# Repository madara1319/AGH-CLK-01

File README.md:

# AGH-CLK-01

Project of embedded wristwatch module powered by li-pol cell realised for University course Design-Laboratory
## Project assumptions
The main goal is to make self-contained embedded wristwatch module that could be used with dedicated wrist as a complete wristwatch. That device will have his own supply made by li-pol cell with dedicated hardware driver. As a display will be used full color LCD screen module with 240x240px and ST7789 driver. Device will be controlled by microprocessor STM32 (particular type will be pick in time) that would be placed on a dedicated printed circuit board “AGH-CLK-01” with the rest of peripherals. Everything should be assembled as a ready-to-use device.

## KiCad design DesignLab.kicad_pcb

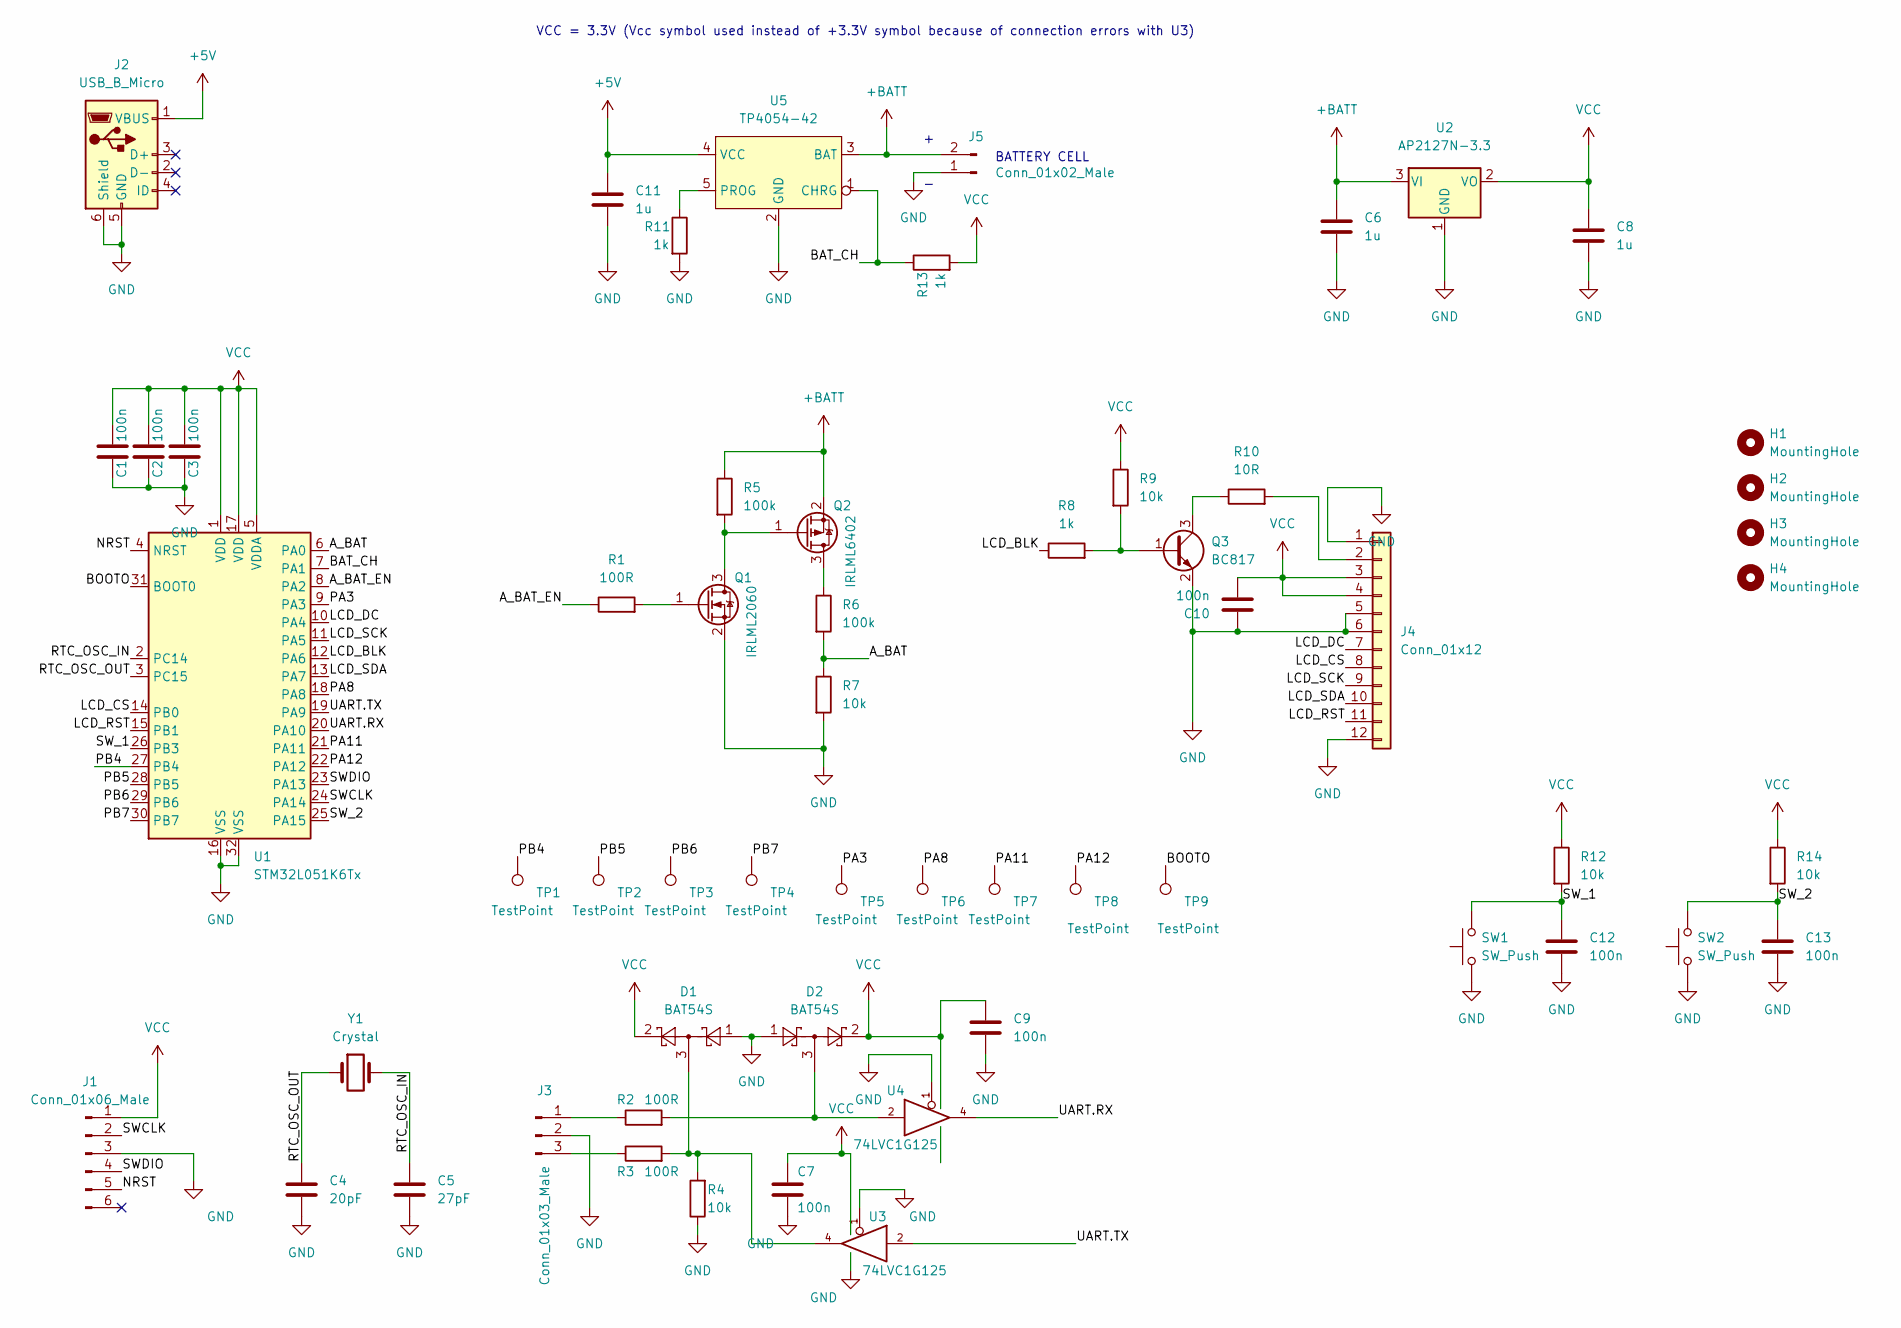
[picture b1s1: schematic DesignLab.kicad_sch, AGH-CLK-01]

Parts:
C1, C2, C3: 100n; C_0603_1608Metric_Pad1.08x0.95mm_HandSolder
C4: 20pF; C_0603_1608Metric_Pad1.08x0.95mm_HandSolder
C5: 27pF; C_0603_1608Metric_Pad1.08x0.95mm_HandSolder
C6, C8: 1u; C_0805_2012Metric_Pad1.18x1.45mm_HandSolder
C7, C9, C10, C12, C13: 100n; C_0805_2012Metric_Pad1.18x1.45mm_HandSolder
C11: 1u; C_1206_3216Metric_Pad1.33x1.80mm_HandSolder
D1, D2: BAT54S; SOT-23
H1, H2, H3, H4: MountingHole; MountingHole_2.2mm_M2_ISO7380
J1: Conn_01x06_Male; PinHeader_2x03_P2.54mm_Vertical
J2: USB_B_Micro; USB_Micro-B_Amphenol_10118194_Horizontal
J3: Conn_01x03_Male; PinHeader_1x03_P2.54mm_Vertical
J4: Conn_01x12; Flex_Tape_12x0.635
J5: Conn_01x02_Male; PinHeader_1x02_P2.54mm_Vertical
Q1: IRLML2060; SOT-23
Q2: IRLML6402; SOT-23
Q3: BC817; SOT-23
R1, R2, R3: 100R; R_0603_1608Metric_Pad0.98x0.95mm_HandSolder
R4, R7, R9, R12, R14: 10k; R_0603_1608Metric_Pad0.98x0.95mm_HandSolder
R5, R6: 100k; R_0603_1608Metric_Pad0.98x0.95mm_HandSolder
R8, R11, R13: 1k; R_0603_1608Metric_Pad0.98x0.95mm_HandSolder
R10: 10R; R_0603_1608Metric_Pad0.98x0.95mm_HandSolder
SW1, SW2: SW_Push; SW_SPST_TSS02-035NT
TP1, TP2, TP3, TP4, TP5, TP6, TP7, TP8, TP9: TestPoint; TestPoint_Pad_1.5x1.5mm
U1: STM32L051K6Tx; LQFP-32_7x7mm_P0.8mm
U2: AP2127N-3.3; SOT-23
U3, U4: 74LVC1G125; SOT-23-5_HandSoldering
U5: TP4054-42; SOT-23-5_HandSoldering
Y1: Crystal; Crystal_SMD_3215-2Pin_3.2x1.5mm

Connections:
+5V: C11.1, J2.1 (VBUS), U5.4 (VCC)
+BATT: C6.1, J5.2, Q2.2 (S), R5.1, U2.3 (VI), U5.3 (BAT)
/A_BAT: R6.2, R7.1, U1.6 (PA0)
/A_BAT_EN: R1.1, U1.8 (PA2)
/BAT_CH: R13.1, U1.7 (PA1), U5.1 (CHRG)
/BOOTO: TP9.1, U1.31 (BOOT0)
/LCD_BLK: R8.1, U1.12 (PA6)
/LCD_CS: J4.8, U1.14 (PB0)
/LCD_DC: J4.7, U1.10 (PA4)
/LCD_RST: J4.11, U1.15 (PB1)
/LCD_SCK: J4.9, U1.11 (PA5)
/LCD_SDA: J4.10, U1.13 (PA7)
/NRST: J1.5, U1.4 (NRST)
/PA3: TP5.1, U1.9 (PA3)
/PA8: TP6.1, U1.18 (PA8)
/PA11: TP7.1, U1.21 (PA11)
/PA12: TP8.1, U1.22 (PA12)
/PB4: TP1.1, U1.27 (PB4)
/PB5: TP2.1, U1.28 (PB5)
/PB6: TP3.1, U1.29 (PB6)
/PB7: TP4.1, U1.30 (PB7)
/RTC_OSC_IN: C5.1, U1.2 (PC14), Y1.2
/RTC_OSC_OUT: C4.1, U1.3 (PC15), Y1.1
/SWCLK: J1.2, U1.24 (PA14)
/SWDIO: J1.4, U1.23 (PA13)
/SW_1: C12.1, R12.2, SW1.2, U1.26 (PB3)
/SW_2: C13.1, R14.2, SW2.2, U1.25 (PA15)
/UART.RX: U1.20 (PA10), U4.4
/UART.TX: U1.19 (PA9), U3.2
GND: C1.2, C2.2, C3.2, C4.2, C5.2, C6.2, C7.2, C8.2, C9.2, C10.1, C11.2, C12.2, C13.2, D1.1, D2.1, J1.3, J2.5 (GND), J2.6 (Shield), J3.2, J4.1, J4.5, J4.6, J4.12, J5.1, Q1.2 (S), Q3.2 (E), R4.1, R7.2, R11.2, SW1.1, SW2.1, U1.16 (VSS), U1.32 (VSS), U2.1 (GND), U3.1, U3.3 (GND), U4.1, U4.3 (GND), U5.2 (GND)
unnamed: D1.3, R3.2, R4.2, U3.4
unnamed: D2.3, R2.2, U4.2
unnamed: J3.1, R2.1
unnamed: J3.3, R3.1
unnamed: J4.2, R10.2
unnamed: Q1.1 (G), R1.2
unnamed: Q1.3 (D), Q2.1 (G), R5.2
unnamed: Q2.3 (D), R6.1
unnamed: Q3.1 (B), R8.2, R9.2
unnamed: Q3.3 (C), R10.1
unnamed: R11.1, U5.5 (PROG)
VCC: C1.1, C2.1, C3.1, C7.1, C8.1, C9.1, C10.2, D1.2, D2.2, J1.1, J4.3, J4.4, R9.1, R12.1, R13.2, R14.1, U1.1 (VDD), U1.5 (VDDA), U1.17 (VDD), U2.2 (VO), U3.5 (VCC), U4.5 (VCC)

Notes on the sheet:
VCC = 3.3V (Vcc symbol used instead of +3.3V symbol because of connection errors with U3)
BATTERY CELL

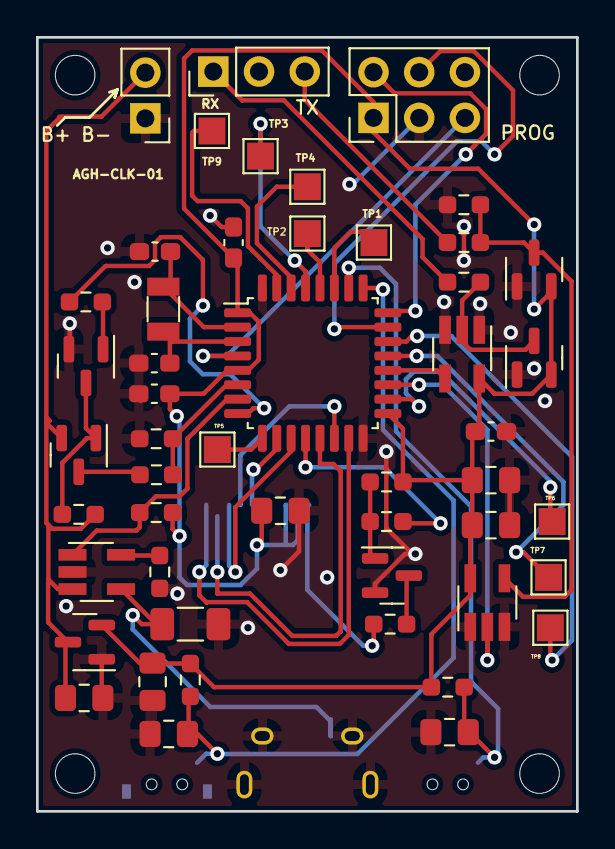
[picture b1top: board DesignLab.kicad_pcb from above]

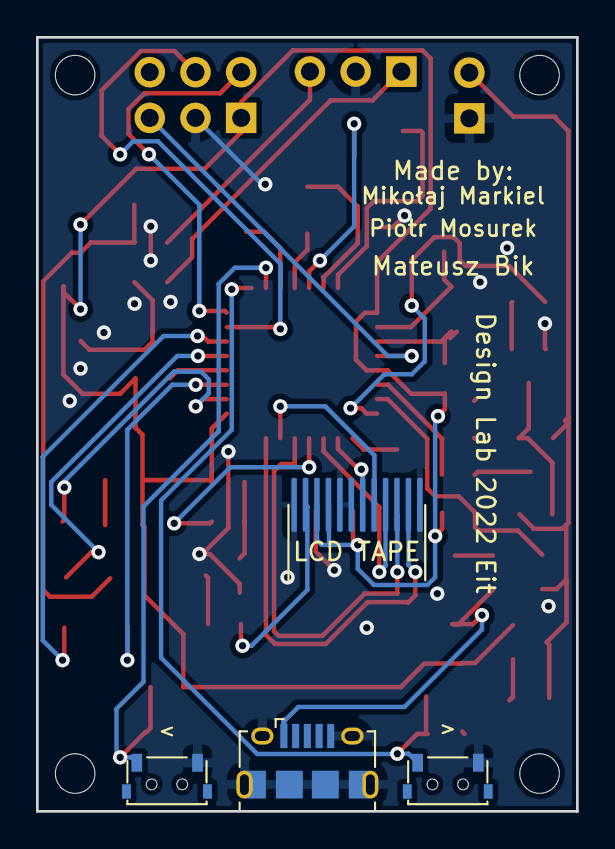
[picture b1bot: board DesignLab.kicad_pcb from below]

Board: 2 copper layers, 30.0 x 43.0 mm, 58 parts (4 on the bottom side), 42 nets.

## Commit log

2022-12-01 Added readme
2022-12-01 Still needs work with connecting correct pins, buffers etc
2022-12-06 v0.2 06.12.2022 MM
    Completed schematic file
2022-12-06 v0.3
    Updated BOM
2022-12-06 Added elementy do zakupu
2022-12-06 Dodano elementy do zakupu
2022-12-07 Edycja elementow
2022-12-07 added shopping list pics
2022-12-07 added pics to elementy
2022-12-08 v0.4 - MM - updated schematic
2022-12-08 Create sdaf.txt
    plik testowy
2022-12-08 Delete sdaf.txt
    dsa
2022-12-08 v0.5 updated schematic
    changed quartz symbol, changed switch footprints, added folder lib/footprints with necessary contents
2022-12-09 v0.6 updated schematic + footprints
2022-12-09 zmiany 9.12 15:00
    brak c11-c13 w schemacie pcb, próby autoroutingu
2022-12-09 edit
    edit
2022-12-10 c
    zmiana w c11 i c12 jednostki farad dalsze problemy z c10-c13 przy dodaniu na pcb
2022-12-12 v0.8 updated layout
2022-12-12 v0.9 updated schematic
2022-12-12 layout PCB draw 0.1version
    prawie skończone
2022-12-13 Layout PCB v0.2
    almost finish layout pcb without error
